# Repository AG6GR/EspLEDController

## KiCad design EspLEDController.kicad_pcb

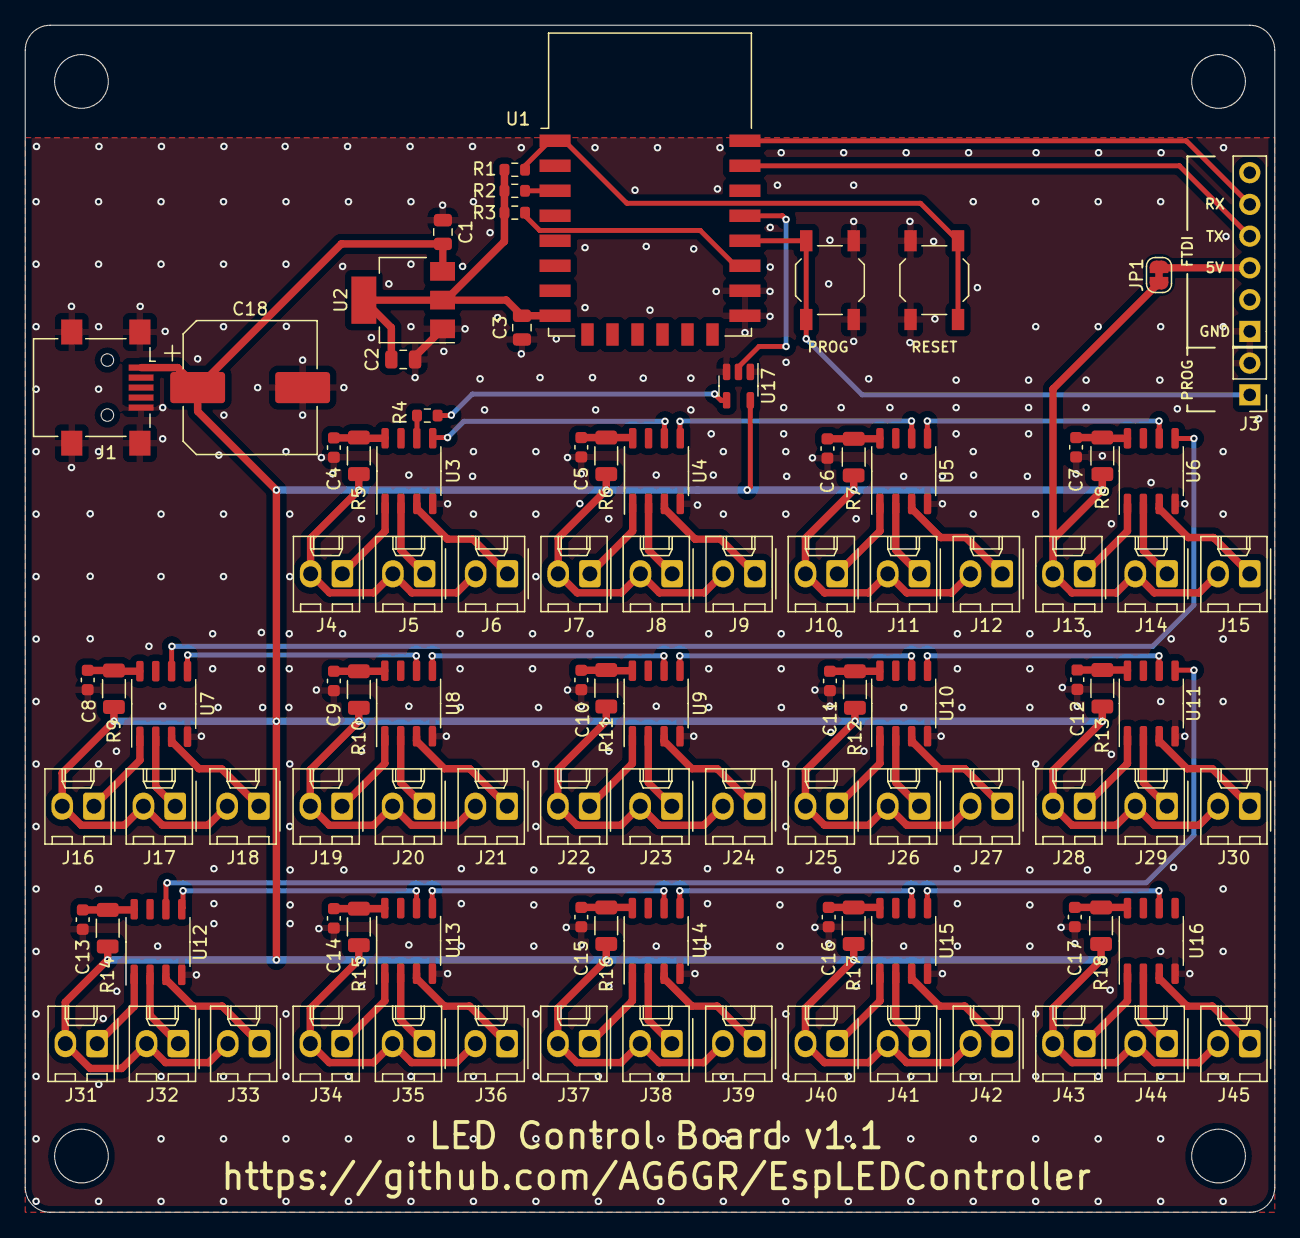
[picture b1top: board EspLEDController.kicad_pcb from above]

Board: 4 copper layers, 100.0 x 95.0 mm, 105 parts (0 on the bottom side), 82 nets.

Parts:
C1, C2, C3: 10u; C_0805_2012Metric
C4, C5, C6, C7, C8, C9, C10, C11, C12, C13, C14, C15, C16, C17: 0.1u; C_0603_1608Metric
C18: 1000u; CP_Elec_10x10.5
H1, H2, H3, H4: MountingHole; MountingHole_4.3mm_M4
J1: USB_B_Micro; USB_Mini-B_Lumberg_2486_01_Horizontal
J2: FTDI; PinHeader_1x06_P2.54mm_Vertical
J3: FLASH; PinHeader_1x02_P2.54mm_Vertical
J4, J5, J6, J7, J8, J9, J10, J11, J12, J13, J14, J15, J16, J17, J18, J19, J20, J21, J22, J23, J24, J25, J26, J27, J28, J29, J30, J31, J32, J33, J34, J35, J36, J37, J38, J39, J40, J41, J42, J43, J44, J45: Conn_01x02; Molex_KK-254_AE-6410-02A_1x02_P2.54mm_Vertical
JP1: SolderJumper_2_Bridged; SolderJumper-2_P1.3mm_Bridged_RoundedPad1.0x1.5mm
R1, R2, R3: 10k; R_0603_1608Metric
R4: 330; R_0603_1608Metric
R5, R6, R7, R8, R9, R10, R11, R12, R13, R14, R15, R16, R17, R18: 100; R_1206_3216Metric
SW1: RESET; SW_SPST_TL3342
SW2: FLASH; SW_SPST_TL3342
U1: ESP-12F; ESP-12E
U2: AMS1117-3.3; SOT-223-3_TabPin2
U3, U4, U5, U6, U7, U8, U9, U10, U11, U12, U13, U14, U15, U16: WS2811; SOP-8_3.9x4.9mm_P1.27mm
U17: 74AHCT1G125; SOT-23-5

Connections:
+3.3V: C2.1, C3.1, R1.1, R2.1, R3.1, U1.8 (VCC), U2.2 (VO)
+5V: C1.1, C18.1, J1.1 (VBUS), J4.2, J5.2, J6.2, J7.2, J8.2, J9.2, J10.2, J11.2, J12.2, J13.2, J14.2, J15.2, J16.2, J17.2, J18.2, J19.2, J20.2, J21.2, J22.2, J23.2, J24.2, J25.2, J26.2, J27.2, J28.2, J29.2, J30.2, J31.2, J32.2, J33.2, J34.2, J35.2, J36.2, J37.2, J38.2, J39.2, J40.2, J41.2, J42.2, J43.2, J44.2, J45.2, JP1.1 (A), R5.1, R6.1, R7.1, R8.1, R9.1, R10.1, R11.1, R12.1, R13.1, R14.1, R15.1, R16.1, R17.1, R18.1, U2.3 (VI), U17.5 (VCC)
/WS2811Unit1/DO: U4.5 (DO), U5.6 (DIN)
/WS2811Unit2/DO: U5.5 (DO), U6.6 (DIN)
/WS2811Unit3/DO: U6.5 (DO), U7.6 (DIN)
/WS2811Unit4/DO: U7.5 (DO), U8.6 (DIN)
/WS2811Unit5/DO: U8.5 (DO), U9.6 (DIN)
/WS2811Unit6/DO: U9.5 (DO), U10.6 (DIN)
/WS2811Unit7/DO: U10.5 (DO), U11.6 (DIN)
/WS2811Unit8/DO: U11.5 (DO), U12.6 (DIN)
/WS2811Unit10/DIN: U13.5 (DO), U14.6 (DIN)
/WS2811Unit10/DO: U14.5 (DO), U15.6 (DIN)
/WS2811Unit11/DIN: U12.5 (DO), U13.6 (DIN)
/WS2811Unit13/DO: U15.5 (DO), U16.6 (DIN)
/WS2811Unit/DIN: R4.2, U3.6 (DIN)
/WS2811Unit/DO: U3.5 (DO), U4.6 (DIN)
FLASH: J3.1, SW2.2, U1.18 (GPIO0)
GND: C1.2, C2.2, C3.2, C4.2, C5.2, C6.2, C7.2, C8.2, C9.2, C10.2, C11.2, C12.2, C13.2, C14.2, C15.2, C16.2, C17.2, C18.2, J1.5 (GND), J1.6 (Shield), J2.1, J3.2, SW1.1, SW2.1, U1.15 (GND), U1.16 (GPIO15), U2.1 (GND), U3.4 (GND), U4.4 (GND), U5.4 (GND), U6.4 (GND), U7.4 (GND), U8.4 (GND), U9.4 (GND), U10.4 (GND), U11.4 (GND), U12.4 (GND), U13.4 (GND), U14.4 (GND), U15.4 (GND), U16.4 (GND), U17.1, U17.3 (GND)
LED_GPIO: U1.19 (GPIO4), U17.2
unnamed: C4.1, R5.2, U3.8 (VDD)
unnamed: C5.1, R6.2, U4.8 (VDD)
unnamed: C6.1, R7.2, U5.8 (VDD)
unnamed: C7.1, R8.2, U6.8 (VDD)
unnamed: C8.1, R9.2, U7.8 (VDD)
unnamed: C9.1, R10.2, U8.8 (VDD)
unnamed: C10.1, R11.2, U9.8 (VDD)
unnamed: C11.1, R12.2, U10.8 (VDD)
unnamed: C12.1, R13.2, U11.8 (VDD)
unnamed: C13.1, R14.2, U12.8 (VDD)
unnamed: C14.1, R15.2, U13.8 (VDD)
unnamed: C15.1, R16.2, U14.8 (VDD)
unnamed: C16.1, R17.2, U15.8 (VDD)
unnamed: C17.1, R18.2, U16.8 (VDD)
unnamed: J2.3, JP1.2 (B)
unnamed: J4.1, U3.1 (OUTR)
unnamed: J5.1, U3.2 (OUTG)
unnamed: J6.1, U3.3 (OUTB)
unnamed: J7.1, U4.1 (OUTR)
unnamed: J8.1, U4.2 (OUTG)
unnamed: J9.1, U4.3 (OUTB)
unnamed: J10.1, U5.1 (OUTR)
unnamed: J11.1, U5.2 (OUTG)
unnamed: J12.1, U5.3 (OUTB)
unnamed: J13.1, U6.1 (OUTR)
unnamed: J14.1, U6.2 (OUTG)
unnamed: J15.1, U6.3 (OUTB)
unnamed: J16.1, U7.1 (OUTR)
unnamed: J17.1, U7.2 (OUTG)
unnamed: J18.1, U7.3 (OUTB)
unnamed: J19.1, U8.1 (OUTR)
unnamed: J20.1, U8.2 (OUTG)
unnamed: J21.1, U8.3 (OUTB)
unnamed: J22.1, U9.1 (OUTR)
unnamed: J23.1, U9.2 (OUTG)
unnamed: J24.1, U9.3 (OUTB)
unnamed: J25.1, U10.1 (OUTR)
unnamed: J26.1, U10.2 (OUTG)
unnamed: J27.1, U10.3 (OUTB)
unnamed: J28.1, U11.1 (OUTR)
unnamed: J29.1, U11.2 (OUTG)
unnamed: J30.1, U11.3 (OUTB)
unnamed: J31.1, U12.1 (OUTR)
unnamed: J32.1, U12.2 (OUTG)
unnamed: J33.1, U12.3 (OUTB)
unnamed: J34.1, U13.1 (OUTR)
unnamed: J35.1, U13.2 (OUTG)
unnamed: J36.1, U13.3 (OUTB)
unnamed: J37.1, U14.1 (OUTR)
unnamed: J38.1, U14.2 (OUTG)
unnamed: J39.1, U14.3 (OUTB)
unnamed: J40.1, U15.1 (OUTR)
unnamed: J41.1, U15.2 (OUTG)
unnamed: J42.1, U15.3 (OUTB)
unnamed: J43.1, U16.1 (OUTR)
unnamed: J44.1, U16.2 (OUTG)
unnamed: J45.1, U16.3 (OUTB)
unnamed: R2.2, U1.3 (EN)
unnamed: R3.2, U1.17 (GPIO2)
unnamed: R4.1, U17.4
RESET: R1.2, SW1.2, U1.1 (~RST)
UART0_RX: J2.4, U1.21 (GPIO3/RXD)
UART0_TX: J2.5, U1.22 (GPIO1/TXD)

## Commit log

2022-09-19 v1.1 Fix LED headers, FTDI power
    Fixes from first board rev:
    - Fix LEDs to be between power and driver output
    - Change FTDI header power to 5V
    - Remove now redundant diode on FTDI power input
2022-12-27 Fix incorrect ESP8266 GPIO pin
